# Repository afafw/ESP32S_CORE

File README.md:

# ESP32S_CORE
一个超小廉价并且尽量保证可以手工焊接的esp32s之类的模块可用的开发板 尺寸2.7x4.88cm
小料基本上都是0603大小的0.1uf，10uf电容和0603 的10k电阻，同时esp32的焊盘选择了较宽的，基本保证有电烙铁就可以了（当然模块底下的地没链接性能不会很好）
bom成本（不包括模块）（不包括ch340c接口按键，模块）：大概1.3左右
加上ch340c，接口和按键也在3元附近。
至于esp32s模块 可以买全新的也可以选择闲鱼（笑）
通过各种手段压低成本（手焊，闲鱼等等）之后开发板成本可以在8元以下,弥补之前消失的9.9包邮开发板。
A cheap, small, hand solderable solution to use many expressif chip including esp32s2,esp32solo1,(any module with same design)

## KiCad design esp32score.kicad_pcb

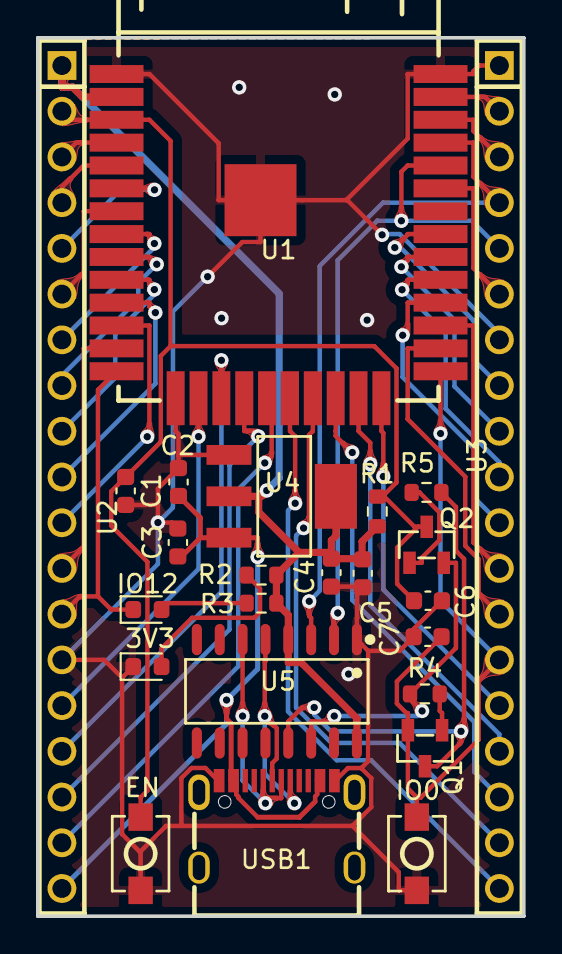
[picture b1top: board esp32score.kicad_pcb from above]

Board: 2 copper layers, 27.0 x 48.8 mm, 24 parts (0 on the bottom side), 44 nets.

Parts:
3V3: LED; LED_0603_1608Metric
C1, C3, C5, C6, C7: 10uf; C_0603_1608Metric
C2, C4: 0.1uf; C_0603_1608Metric
EN: TS-1088-AR02016; SW-SMD_L4.0-W2.9-LS5.0
IO0: TS-1088-AR02016; SW-SMD_L4.0-W2.9-LS5.0
IO12: LED; LED_0603_1608Metric
Q1, Q2: SS8050_C2150; SOT-23-3_L2.9-W1.3-P1.90-LS2.4-BR
R1, R2, R3, R4, R5: 10k; R_0603_1608Metric
U1: ESP32-S; WIRELM-SMD_ESP32-S
U2, U3: HDR_2.54-1x19P; HDR-TH_19P-P2.54-V-M
U4: AMS1117-3.3; SOT-223-3_L6.5-W3.4-P2.30-LS7.0-BR
U5: CH340C; SOP-16_L10.0-W3.9-P1.27-LS6.0-BL
USB1: KH-TYPE-C-16P; USB-C-SMD_KH-TYPE-C-16P

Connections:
+3.3V: C4.1, C5.1, R1.1, R2.1, R3.1, U1.2 (3V3), U2.1, U4.2 (VOUT), U4.4 (VOUT), U5.4 (V3), U5.16 (VCC)
+5V: C2.1, C3.1, U2.19, U4.3 (VIN), USB1.A4 (VBUS), USB1.A9 (VBUS), USB1.B4 (VBUS), USB1.B9 (VBUS)
CLK: U1.20 (CLK), U3.19
CMD: U1.19 (CMD), U2.18
D+: U5.5 (D+), USB1.A6 (DP1), USB1.B6 (DP2)
D-: U5.6 (D-), USB1.A7 (DN1), USB1.B7 (DN2)
DTR: Q1.3 (C), R5.1, U5.13 (DTR#)
EN: C1.1, C6.1, EN.1, Q2.3 (C), R1.2, U1.3 (EN), U2.2
GND: 3V3.1 (K), C1.2, C2.2, C3.2, C4.2, C5.2, C6.2, C7.2, EN.2, IO0.2, U1.1 (GND), U1.15 (GND), U1.38 (GND), U1.39 (EP), U2.14, U3.1, U3.7, U4.1 (GND), U5.1 (GND), USB1.A1 (GND), USB1.A12 (GND), USB1.B1 (GND), USB1.B12 (GND)
GPIO2: U1.24 (IO2), U3.15
GPIO4: U1.26 (IO4), U3.13
GPIO5: U1.29 (IO5), U3.10
GPIO12: IO12.1 (K), U1.14 (IO12), U2.13
GPIO13: U1.16 (IO13), U2.15
GPIO14: U1.13 (IO14), U2.12
GPIO15: U1.23 (IO15), U3.16
GPIO16: U1.27 (IO16), U3.12
GPIO17: U1.28 (IO17), U3.11
GPIO18: U1.30 (IO18), U3.9
GPIO19: U1.31 (IO19), U3.8
GPIO21: U1.33 (IO21), U3.6
GPIO22: U1.36 (IO22), U3.3
GPIO23: U1.37 (IO23), U3.2
GPIO25: U1.10 (IO25), U2.9
GPIO26: U1.11 (IO26), U2.10
GPIO27: U1.12 (IO27), U2.11
GPIO32: U1.8 (IO32), U2.7
GPIO33: U1.9 (IO33), U2.8
GPIO34: U1.6 (IO34), U2.5
GPIO35: U1.7 (IO35), U2.6
IO0: C7.1, IO0.1, Q1.2 (E), U1.25 (IO0), U3.14
unnamed: 3V3.2 (A), R2.2
unnamed: IO12.2 (A), R3.2
unnamed: Q1.1 (B), R4.2
unnamed: Q2.1 (B), R5.2
RTS: Q2.2 (E), R4.1, U5.14 (RTS#)
RXD: U1.34 (U0RXD), U3.5, U5.2 (TXD)
SD0: U1.21 (SDO), U3.18
SD1: U1.22 (SDI), U3.17
SD2: U1.17 (SD2), U2.16
SD3: U1.18 (SD3), U2.17
SENSOR VN: U1.5 (SENSOR_VN), U2.4
SENSOR VP: U1.4 (SENSOR_VP), U2.3
TXD: U1.35 (U0TXD), U3.4, U5.3 (RXD)

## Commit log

2022-08-23 Create LICENSE
